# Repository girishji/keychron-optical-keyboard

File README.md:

# Keychron Low-Pro Optical Keyboard
Keyboard PCB in KiCad using Keychron low-profile optical switches, with some ergonomic sugar and integrated wrist rest.

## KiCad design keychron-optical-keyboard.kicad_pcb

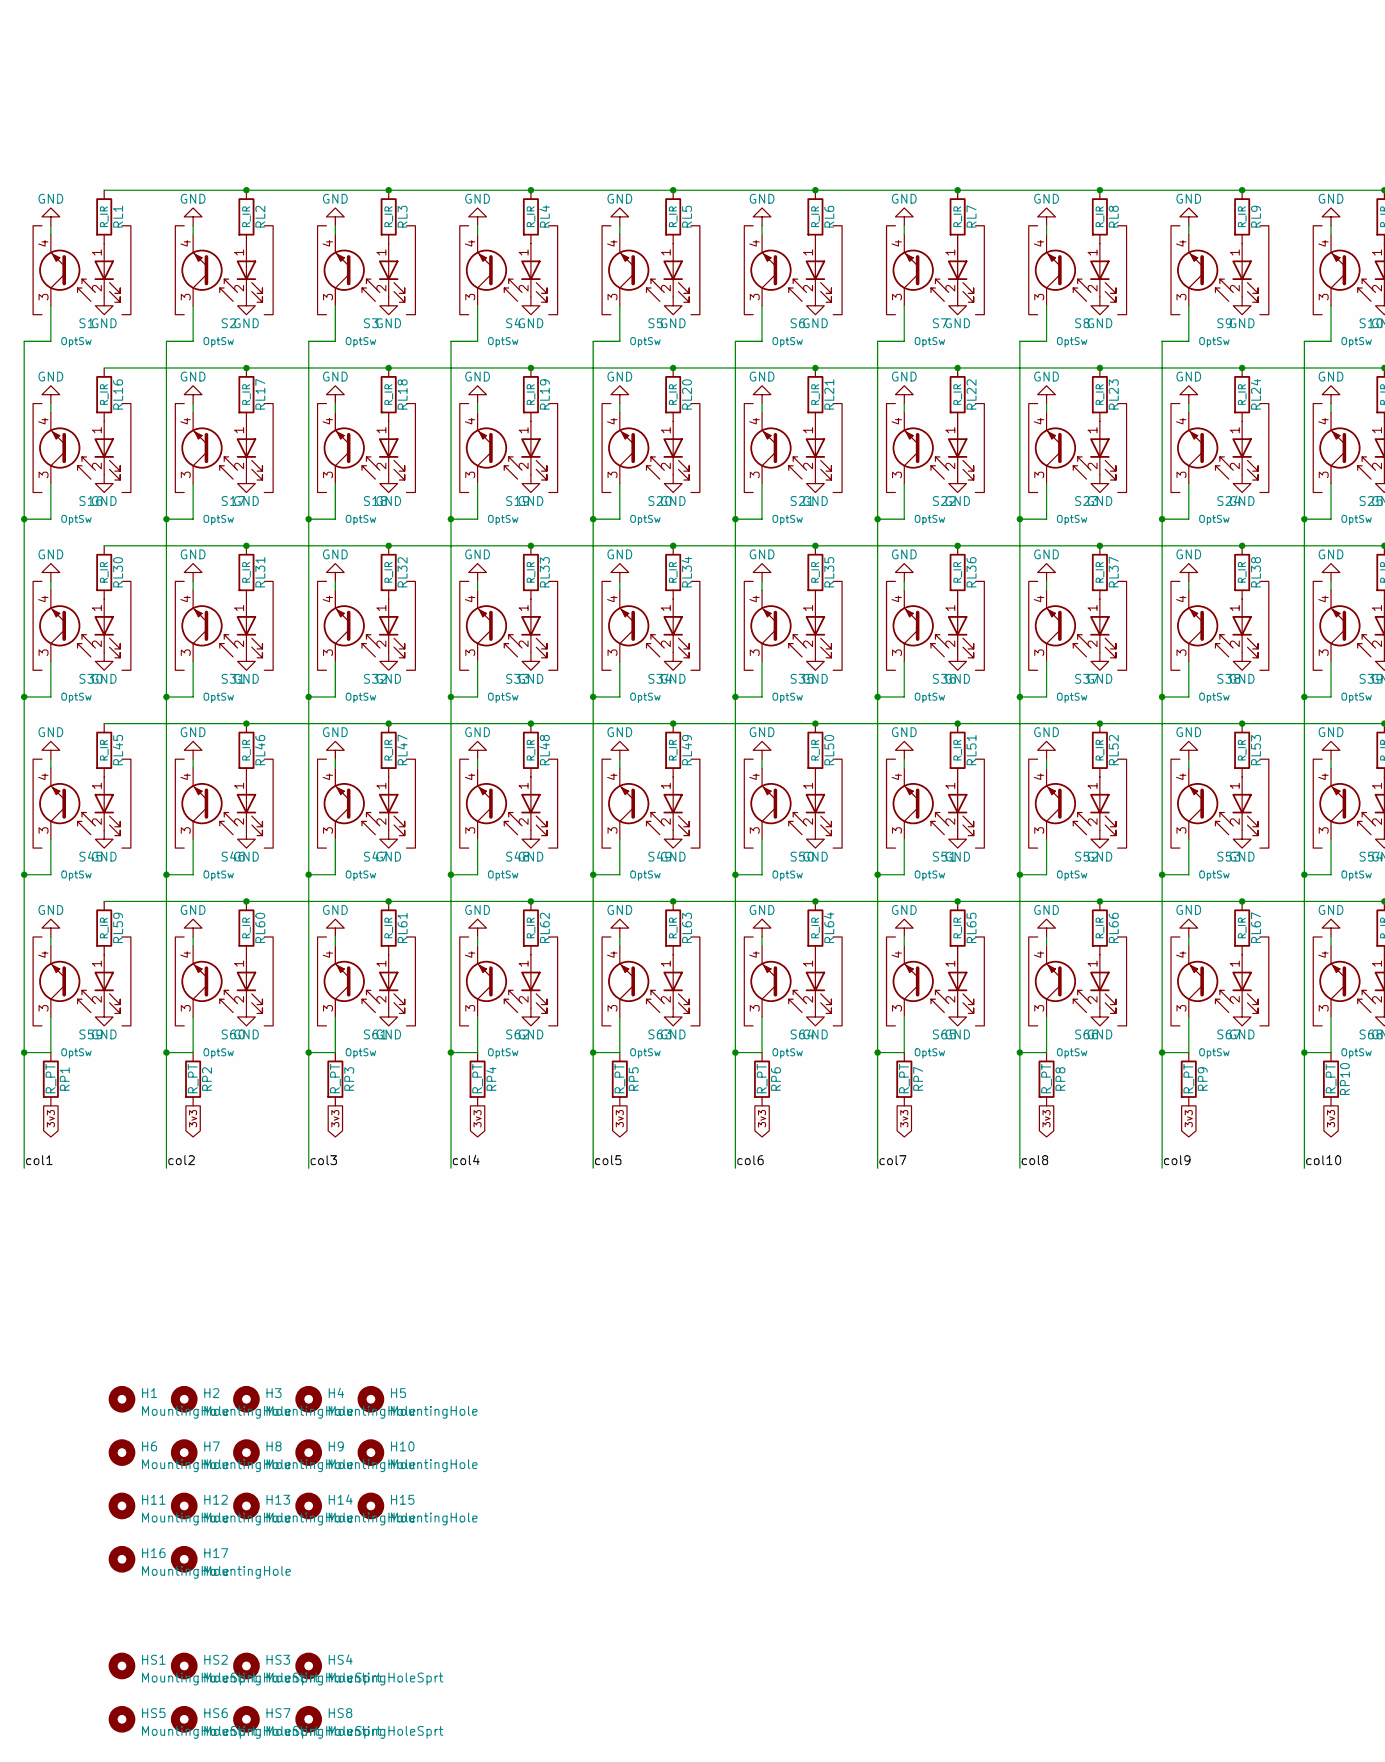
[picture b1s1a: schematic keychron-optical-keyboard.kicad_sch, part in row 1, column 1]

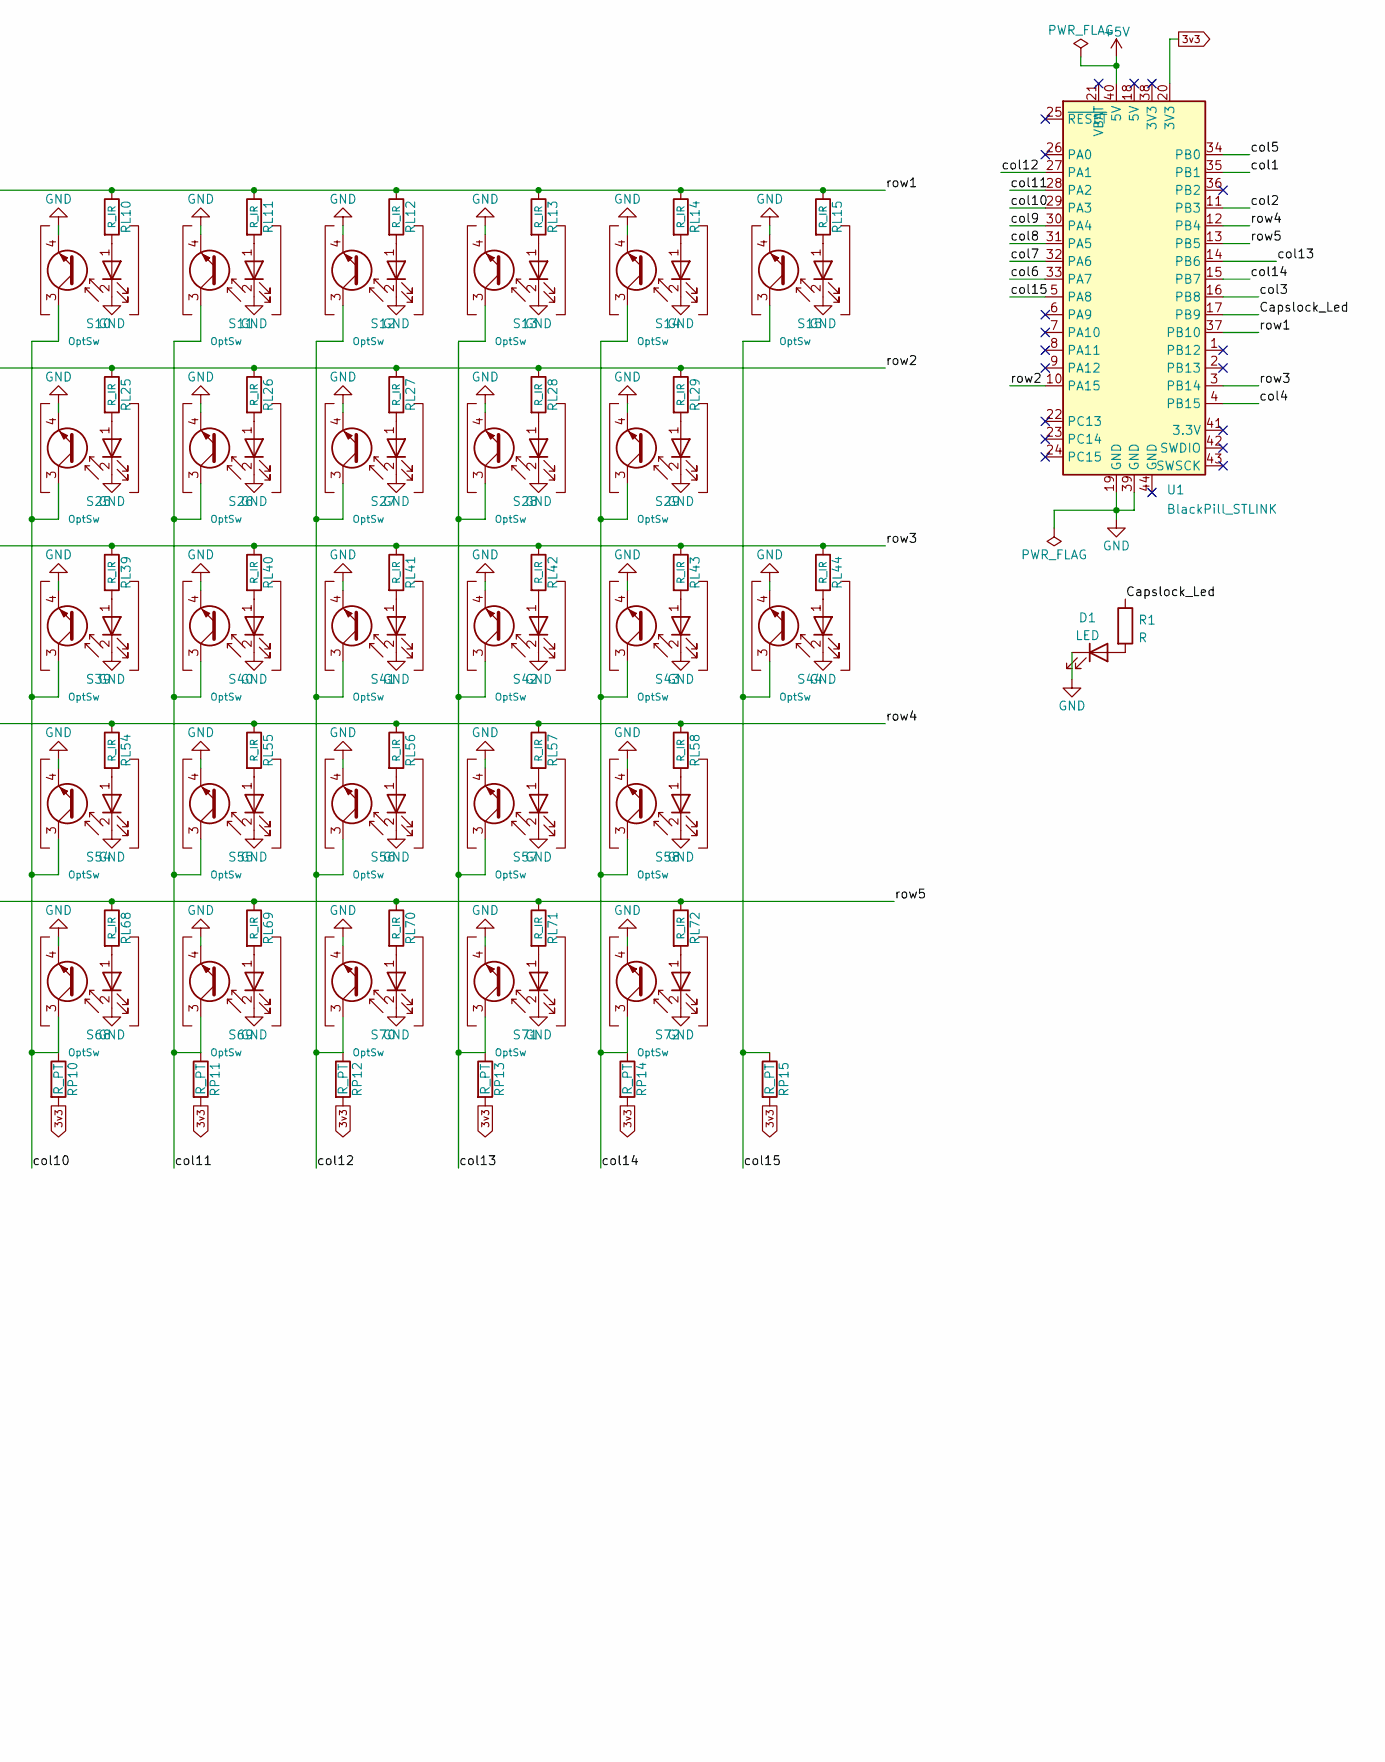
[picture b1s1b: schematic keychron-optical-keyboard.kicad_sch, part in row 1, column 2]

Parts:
D1: LED; LED_0603_1608Metric_Pad1.05x0.95mm_HandSolder
H1, H2, H3, H4, H5, H6, H7, H8, H9, H10, H11, H12, H13, H14, H15, H16, H17: MountingHole; SMTSO_M1.6
HS1, HS2, HS3, HS4, HS5, HS6, HS7, HS8: MountingHoleSprt; SMTSO_M2
R1: R; R_0805_2012Metric_Pad1.20x1.40mm_HandSolder
RL1: R_IR; R_0805_2012Metric_Pad1.20x1.40mm_HandSolder
RL2, RL3, RL4, RL5, RL6, RL7, RL8, RL9, RL10, RL11, RL12, RL13, RL14, RL15, RL16, RL17, RL18, RL19, RL20, RL21, RL22, RL23, RL24, RL25, RL26, RL27, RL28, RL29, RL30, RL31, RL32, RL33, RL34, RL35, RL36, RL37, RL38, RL39, RL40, RL41, RL42, RL43, RL44, RL45, RL46, RL47, RL48, RL49, RL50, RL51, RL52, RL53, RL54, RL55, RL56, RL57, RL58, RL59, RL60, RL61, RL62, RL63, RL64, RL65, RL66, RL67, RL68, RL69, RL70, RL71, RL72: R_IR; R_0805_2012Metric_Pad1.20x1.40mm_HandSolder; JLC 0603-1608
RP1, RP2, RP3, RP4, RP5, RP6, RP7, RP8, RP9, RP10, RP11, RP12, RP13, RP14, RP15: R_PT; R_0805_2012Metric_Pad1.20x1.40mm_HandSolder; JLC 0805-2012
S1, S2, S3, S4, S5, S6, S7, S8, S9, S10, S11, S12, S13, S14, S15, S17, S18, S19, S20, S21, S22, S23, S24, S25, S26, S27, S28, S30, S31, S32, S33, S34, S35, S36, S37, S38, S39, S40, S41, S42, S44, S46, S47, S48, S49, S50, S51, S52, S53, S54, S55, S56, S58, S59, S60, S61, S62, S65, S67, S68, S69, S70, S71, S72: OptSw; Keychron_Optical_Switch_1u
S16, S29, S45: OptSw; Keychron_Optical_Switch_1.5u
S43, S57, S63, S64, S66: OptSw; Keychron_Optical_Switch_1.25u
U1: BlackPill_STLINK; BlackPill_STLINK_Down

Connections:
3v3: RP1.2, RP2.2, RP3.2, RP4.2, RP5.2, RP6.2, RP7.2, RP8.2, RP9.2, RP10.2, RP11.2, RP12.2, RP13.2, RP14.2, RP15.2, U1.20 (3V3)
+5V: U1.40 (5V)
/Capslock_Led: R1.1, U1.17 (PB9)
/col1: RP1.1, S1.3 (C), S16.3 (C), S30.3 (C), S45.3 (C), S59.3 (C), U1.35 (PB1)
/col2: RP2.1, S2.3 (C), S17.3 (C), S31.3 (C), S46.3 (C), S60.3 (C), U1.11 (PB3)
/col3: RP3.1, S3.3 (C), S18.3 (C), S32.3 (C), S47.3 (C), S61.3 (C), U1.16 (PB8)
/col4: RP4.1, S4.3 (C), S19.3 (C), S33.3 (C), S48.3 (C), S62.3 (C), U1.4 (PB15)
/col5: RP5.1, S5.3 (C), S20.3 (C), S34.3 (C), S49.3 (C), S63.3 (C), U1.34 (PB0)
/col6: RP6.1, S6.3 (C), S21.3 (C), S35.3 (C), S50.3 (C), S64.3 (C), U1.33 (PA7)
/col7: RP7.1, S7.3 (C), S22.3 (C), S36.3 (C), S51.3 (C), S65.3 (C), U1.32 (PA6)
/col8: RP8.1, S8.3 (C), S23.3 (C), S37.3 (C), S52.3 (C), S66.3 (C), U1.31 (PA5)
/col9: RP9.1, S9.3 (C), S24.3 (C), S38.3 (C), S53.3 (C), S67.3 (C), U1.30 (PA4)
/col10: RP10.1, S10.3 (C), S25.3 (C), S39.3 (C), S54.3 (C), S68.3 (C), U1.29 (PA3)
/col11: RP11.1, S11.3 (C), S26.3 (C), S40.3 (C), S55.3 (C), S69.3 (C), U1.28 (PA2)
/col12: RP12.1, S12.3 (C), S27.3 (C), S41.3 (C), S56.3 (C), S70.3 (C), U1.27 (PA1)
/col13: RP13.1, S13.3 (C), S28.3 (C), S42.3 (C), S57.3 (C), S71.3 (C), U1.14 (PB6)
/col14: RP14.1, S14.3 (C), S29.3 (C), S43.3 (C), S58.3 (C), S72.3 (C), U1.15 (PB7)
/col15: RP15.1, S15.3 (C), S44.3 (C), U1.5 (PA8)
/row1: RL1.1, RL2.1, RL3.1, RL4.1, RL5.1, RL6.1, RL7.1, RL8.1, RL9.1, RL10.1, RL11.1, RL12.1, RL13.1, RL14.1, RL15.1, U1.37 (PB10)
/row2: RL16.1, RL17.1, RL18.1, RL19.1, RL20.1, RL21.1, RL22.1, RL23.1, RL24.1, RL25.1, RL26.1, RL27.1, RL28.1, RL29.1, U1.10 (PA15)
/row3: RL30.1, RL31.1, RL32.1, RL33.1, RL34.1, RL35.1, RL36.1, RL37.1, RL38.1, RL39.1, RL40.1, RL41.1, RL42.1, RL43.1, RL44.1, U1.3 (PB14)
/row4: RL45.1, RL46.1, RL47.1, RL48.1, RL49.1, RL50.1, RL51.1, RL52.1, RL53.1, RL54.1, RL55.1, RL56.1, RL57.1, RL58.1, U1.12 (PB4)
/row5: RL59.1, RL60.1, RL61.1, RL62.1, RL63.1, RL64.1, RL65.1, RL66.1, RL67.1, RL68.1, RL69.1, RL70.1, RL71.1, RL72.1, U1.13 (PB5)
GND: D1.1 (K), S1.2 (IR_K), S1.4 (E), S2.2 (IR_K), S2.4 (E), S3.2 (IR_K), S3.4 (E), S4.2 (IR_K), S4.4 (E), S5.2 (IR_K), S5.4 (E), S6.2 (IR_K), S6.4 (E), S7.2 (IR_K), S7.4 (E), S8.2 (IR_K), S8.4 (E), S9.2 (IR_K), S9.4 (E), S10.2 (IR_K), S10.4 (E), S11.2 (IR_K), S11.4 (E), S12.2 (IR_K), S12.4 (E), S13.2 (IR_K), S13.4 (E), S14.2 (IR_K), S14.4 (E), S15.2 (IR_K), S15.4 (E), S16.2 (IR_K), S16.4 (E), S17.2 (IR_K), S17.4 (E), S18.2 (IR_K), S18.4 (E), S19.2 (IR_K), S19.4 (E), S20.2 (IR_K), S20.4 (E), S21.2 (IR_K), S21.4 (E), S22.2 (IR_K), S22.4 (E), S23.2 (IR_K), S23.4 (E), S24.2 (IR_K), S24.4 (E), S25.2 (IR_K), S25.4 (E), S26.2 (IR_K), S26.4 (E), S27.2 (IR_K), S27.4 (E), S28.2 (IR_K), S28.4 (E), S29.2 (IR_K), S29.4 (E), S30.2 (IR_K), S30.4 (E), S31.2 (IR_K), S31.4 (E), S32.2 (IR_K), S32.4 (E), S33.2 (IR_K), S33.4 (E), S34.2 (IR_K), S34.4 (E), S35.2 (IR_K), S35.4 (E), S36.2 (IR_K), S36.4 (E), S37.2 (IR_K), S37.4 (E), S38.2 (IR_K), S38.4 (E), S39.2 (IR_K), S39.4 (E), S40.2 (IR_K), S40.4 (E), S41.2 (IR_K), S41.4 (E), S42.2 (IR_K), S42.4 (E), S43.2 (IR_K), S43.4 (E), S44.2 (IR_K), S44.4 (E), S45.2 (IR_K), S45.4 (E), S46.2 (IR_K), S46.4 (E), S47.2 (IR_K), S47.4 (E), S48.2 (IR_K), S48.4 (E), S49.2 (IR_K), S49.4 (E), S50.2 (IR_K), S50.4 (E), S51.2 (IR_K), S51.4 (E), S52.2 (IR_K), S52.4 (E), S53.2 (IR_K), S53.4 (E), S54.2 (IR_K), S54.4 (E), S55.2 (IR_K), S55.4 (E), S56.2 (IR_K), S56.4 (E), S57.2 (IR_K), S57.4 (E), S58.2 (IR_K), S58.4 (E), S59.2 (IR_K), S59.4 (E), S60.2 (IR_K), S60.4 (E), S61.2 (IR_K), S61.4 (E), S62.2 (IR_K), S62.4 (E), S63.2 (IR_K), S63.4 (E), S64.2 (IR_K), S64.4 (E), S65.2 (IR_K), S65.4 (E), S66.2 (IR_K), S66.4 (E), S67.2 (IR_K), S67.4 (E), S68.2 (IR_K), S68.4 (E), S69.2 (IR_K), S69.4 (E), S70.2 (IR_K), S70.4 (E), S71.2 (IR_K), S71.4 (E), S72.2 (IR_K), S72.4 (E), U1.19 (GND), U1.39 (GND)
unnamed: D1.2 (A), R1.2
unnamed: RL1.2, S1.1 (IR_A)
unnamed: RL2.2, S2.1 (IR_A)
unnamed: RL3.2, S3.1 (IR_A)
unnamed: RL4.2, S4.1 (IR_A)
unnamed: RL5.2, S5.1 (IR_A)
unnamed: RL6.2, S6.1 (IR_A)
unnamed: RL7.2, S7.1 (IR_A)
unnamed: RL8.2, S8.1 (IR_A)
unnamed: RL9.2, S9.1 (IR_A)
unnamed: RL10.2, S10.1 (IR_A)
unnamed: RL11.2, S11.1 (IR_A)
unnamed: RL12.2, S12.1 (IR_A)
unnamed: RL13.2, S13.1 (IR_A)
unnamed: RL14.2, S14.1 (IR_A)
unnamed: RL15.2, S15.1 (IR_A)
unnamed: RL16.2, S16.1 (IR_A)
unnamed: RL17.2, S17.1 (IR_A)
unnamed: RL18.2, S18.1 (IR_A)
unnamed: RL19.2, S19.1 (IR_A)
unnamed: RL20.2, S20.1 (IR_A)
unnamed: RL21.2, S21.1 (IR_A)
unnamed: RL22.2, S22.1 (IR_A)
unnamed: RL23.2, S23.1 (IR_A)
unnamed: RL24.2, S24.1 (IR_A)
unnamed: RL25.2, S25.1 (IR_A)
unnamed: RL26.2, S26.1 (IR_A)
unnamed: RL27.2, S27.1 (IR_A)
unnamed: RL28.2, S28.1 (IR_A)
unnamed: RL29.2, S29.1 (IR_A)
unnamed: RL30.2, S30.1 (IR_A)
unnamed: RL31.2, S31.1 (IR_A)
unnamed: RL32.2, S32.1 (IR_A)
unnamed: RL33.2, S33.1 (IR_A)
unnamed: RL34.2, S34.1 (IR_A)
unnamed: RL35.2, S35.1 (IR_A)
unnamed: RL36.2, S36.1 (IR_A)
unnamed: RL37.2, S37.1 (IR_A)
unnamed: RL38.2, S38.1 (IR_A)
unnamed: RL39.2, S39.1 (IR_A)
unnamed: RL40.2, S40.1 (IR_A)
unnamed: RL41.2, S41.1 (IR_A)
unnamed: RL42.2, S42.1 (IR_A)
unnamed: RL43.2, S43.1 (IR_A)
unnamed: RL44.2, S44.1 (IR_A)
unnamed: RL45.2, S45.1 (IR_A)
unnamed: RL46.2, S46.1 (IR_A)
unnamed: RL47.2, S47.1 (IR_A)
unnamed: RL48.2, S48.1 (IR_A)
unnamed: RL49.2, S49.1 (IR_A)
unnamed: RL50.2, S50.1 (IR_A)
unnamed: RL51.2, S51.1 (IR_A)
unnamed: RL52.2, S52.1 (IR_A)
unnamed: RL53.2, S53.1 (IR_A)
unnamed: RL54.2, S54.1 (IR_A)
unnamed: RL55.2, S55.1 (IR_A)
unnamed: RL56.2, S56.1 (IR_A)
unnamed: RL57.2, S57.1 (IR_A)
unnamed: RL58.2, S58.1 (IR_A)
unnamed: RL59.2, S59.1 (IR_A)
unnamed: RL60.2, S60.1 (IR_A)
unnamed: RL61.2, S61.1 (IR_A)
unnamed: RL62.2, S62.1 (IR_A)
unnamed: RL63.2, S63.1 (IR_A)
unnamed: RL64.2, S64.1 (IR_A)
unnamed: RL65.2, S65.1 (IR_A)
unnamed: RL66.2, S66.1 (IR_A)
unnamed: RL67.2, S67.1 (IR_A)
unnamed: RL68.2, S68.1 (IR_A)
unnamed: RL69.2, S69.1 (IR_A)
unnamed: RL70.2, S70.1 (IR_A)
unnamed: RL71.2, S71.1 (IR_A)
unnamed: RL72.2, S72.1 (IR_A)

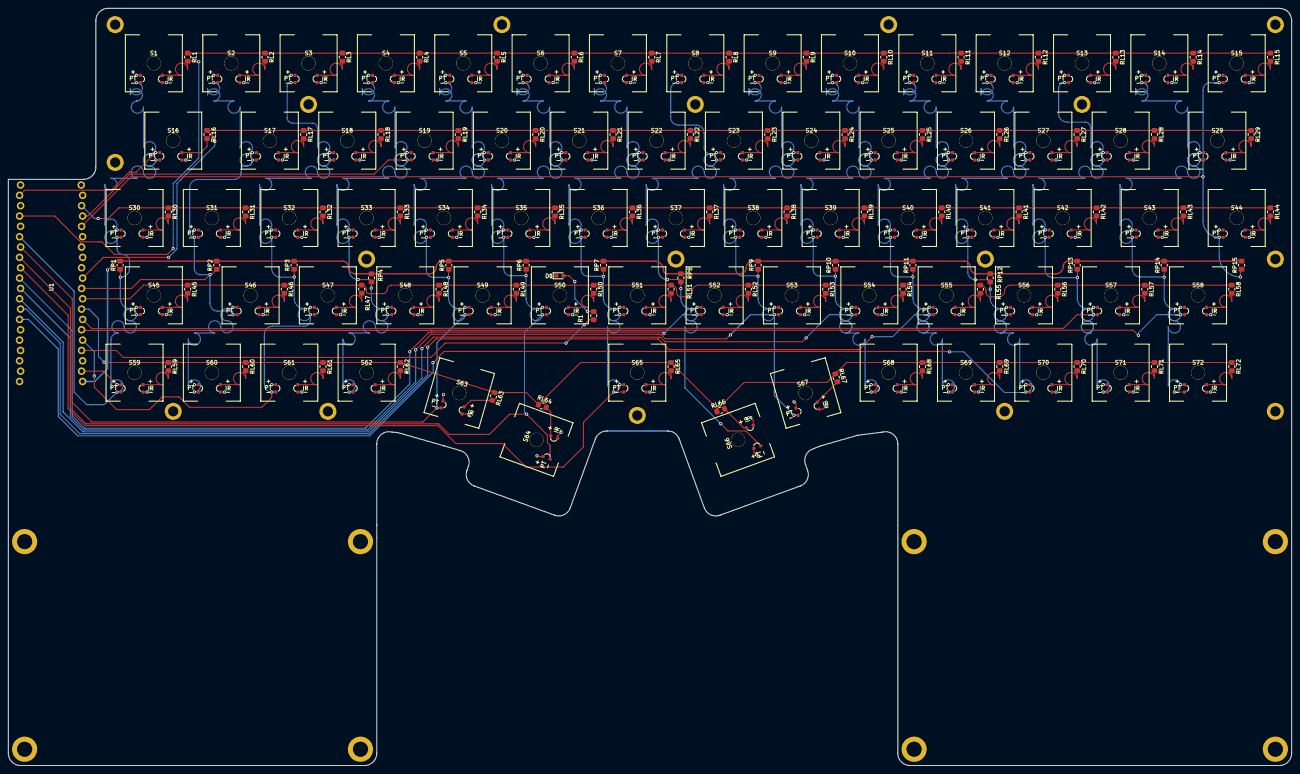
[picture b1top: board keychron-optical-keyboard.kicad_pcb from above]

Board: 2 copper layers, 315.2 x 186.0 mm, 187 parts (0 on the bottom side), 96 nets.

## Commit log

2022-08-03 Add schematic for keyboard and footprints
    M .gitignore
    A Footprints.pretty/BlackPill_STLINK2.kicad_mod
    A Footprints.pretty/IR12-21C_TR8.kicad_mod
    A Footprints.pretty/Keychron_LP_Optical.kicad_mod
    A Footprints.pretty/Keychron_Optical_Switch_1.25u.kicad_mod
    A Footprints.pretty/Keychron_Optical_Switch_1.5u.kicad_mod
2022-08-05 Add footprints
    M .gitignore
    A Footprints.pretty/BlackPill_STLINK.kicad_mod
    M Footprints.pretty/BlackPill_STLINK2.kicad_mod
    M Footprints.pretty/Keychron_Optical_Switch_1.25u.kicad_mod
    M Footprints.pretty/Keychron_Optical_Switch_1.5u.kicad_mod
    M Footprints.pretty/Keychron_Optical_Switch_1.75u.kicad_mod
2022-08-15 Route tracks, add switch plate, scripts
    Add python scripts to route tracks, draw border, place footprints
    A Footprints.pretty/BlackPill_STLINK_Down.kicad_mod
    A Footprints.pretty/Border_PCB_WR.kicad_mod
    M Footprints.pretty/Keychron_Optical_Switch_1.25u.kicad_mod
    M Footprints.pretty/Keychron_Optical_Switch_1.5u.kicad_mod
    D Footprints.pretty/Keychron_Optical_Switch_1.75u.kicad_mod
2022-08-16 Add border to switch plate
    A Footprints.pretty/MountingHole_1.7mm_M1.6_Pad.kicad_mod
    M Footprints.pretty/MountingHole_2.2mm_M2_ISO7380_Pad.kicad_mod
    M placek.py
    M switch-plate/switch-plate.kicad_pcb
    M switch-plate/switch-plate.kicad_sch
2022-08-16 Add wrist support plate and remove 2 keys
    A Footprints.pretty/Keychron_Optical_Switch_1.75u.kicad_mod
    A drawborderk.py
    M keychron-optical-keyboard.kicad_pcb
    M keychron-optical-keyboard.kicad_prl
    M keychron-optical-keyboard.kicad_pro
    M keychron-optical-keyboard.kicad_sch
2022-08-17 Add gerbers and assembly file
    M .gitignore
    M README.md
    A jlcpcb/gerber.zip
    A jlcpcb/gerber/keychron-optical-keyboard-B_Cu.gbl
    A jlcpcb/gerber/keychron-optical-keyboard-B_Mask.gbs
    A jlcpcb/gerber/keychron-optical-keyboard-B_Paste.gbp
